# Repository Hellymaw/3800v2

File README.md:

# 3800v2
A personal re-attempt at ENGG3800 project

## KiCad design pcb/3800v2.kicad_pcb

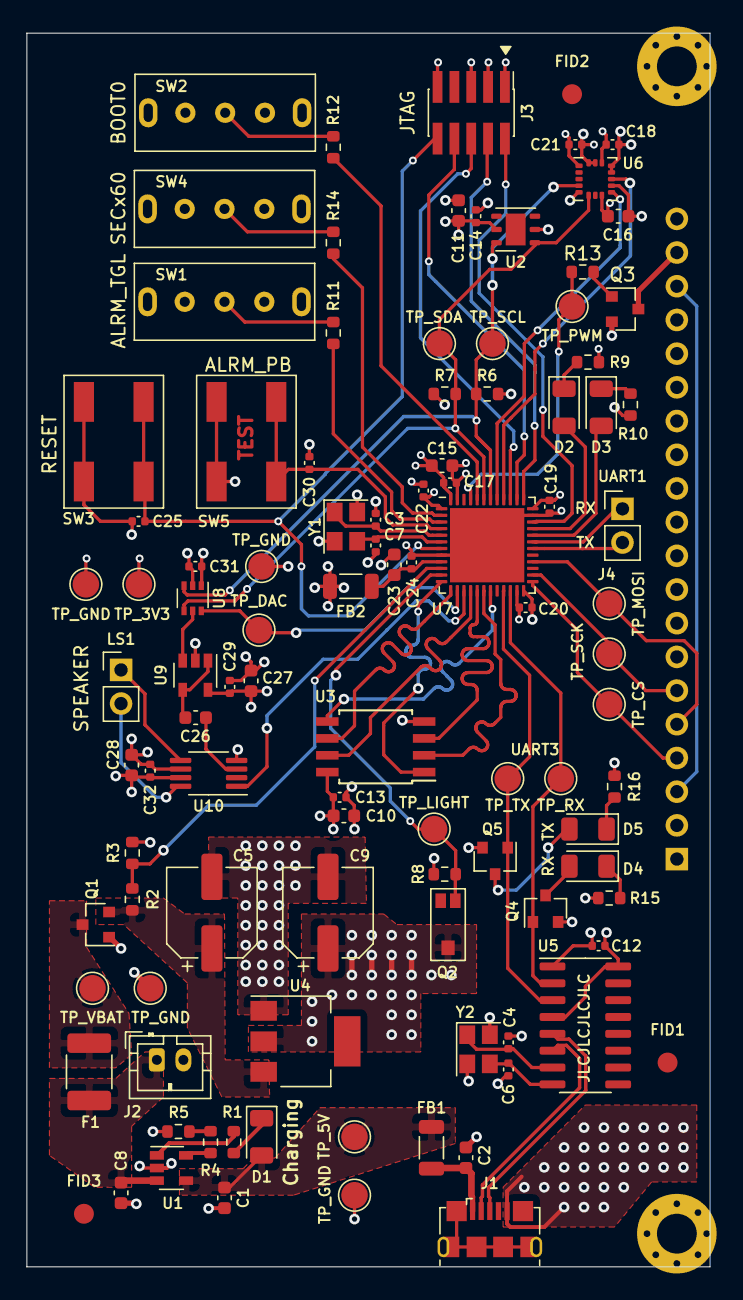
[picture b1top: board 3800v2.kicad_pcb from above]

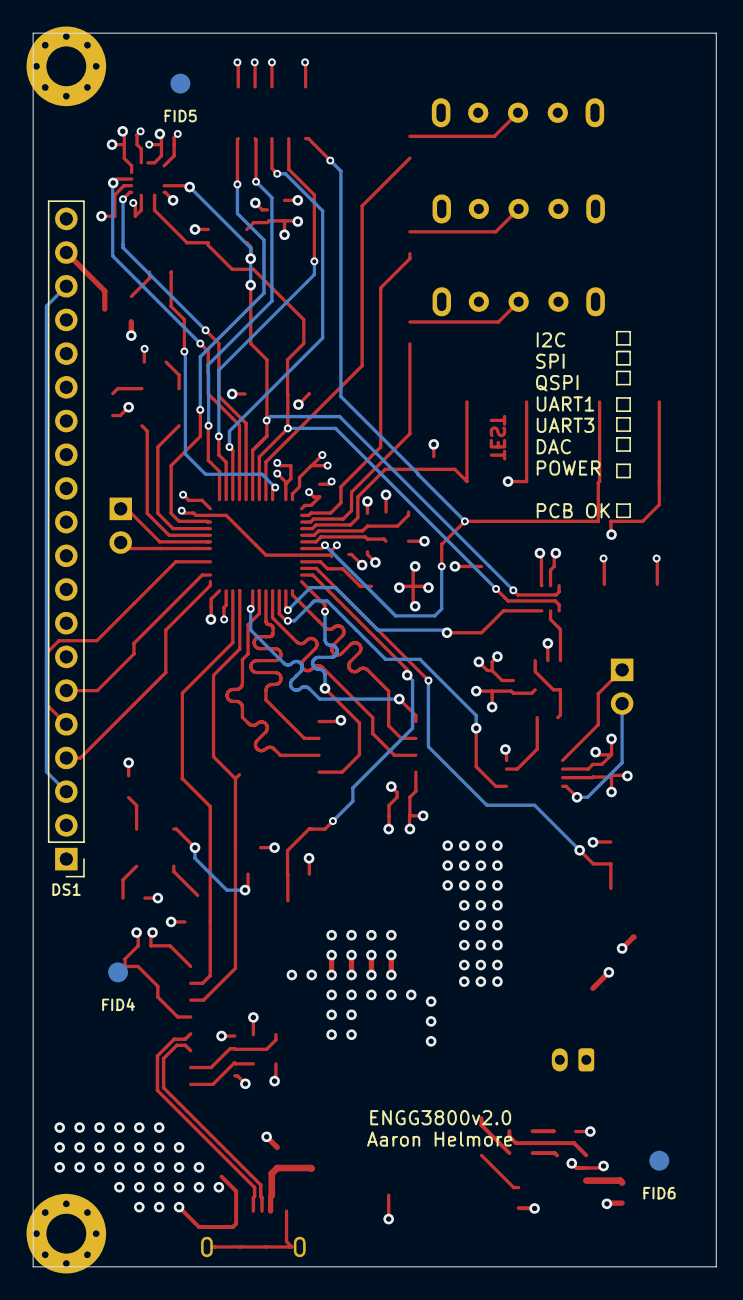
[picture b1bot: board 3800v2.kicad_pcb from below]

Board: 4 copper layers, 51.5 x 93.0 mm, 109 parts (4 on the bottom side), 68 nets.

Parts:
C1, C2, C8, C10, C11, C15, C16, C27, C28: 4.7uF; C_0603_1608Metric
C3, C4, C6, C7: 20pF; C_0402_1005Metric
C5, C9: 47uF; CP_Elec_6.3x7.7
C12, C13, C14, C17, C18, C19, C20, C21, C22, C25, C29, C30, C31, C32: 100nF; C_0402_1005Metric
C23, C26: 1uF; C_0603_1608Metric
C24: 10nF; C_0402_1005Metric
D1, D2, D3, D5: RED; LED_1206_3216Metric
D4: GREEN; LED_1206_3216Metric
DS1: ST7920; PinHeader_1x20_P2.54mm_Vertical
F1: 16V 1.5A; Fuse_1812_4532Metric_Castellated
FB1, FB2: 100 @ 100MHz; L_1206_3216Metric
FID1, FID2, FID3, FID4, FID5, FID6: Fiducial; Fiducial_1.5mm_Mask3mm
H1, H2: M2.5mm; MountingHole_3mm_Pad_Via
J1: USB_B_Micro; USB_Micro-B_Amphenol_10118193_Horizontal
J2: JST PH 1x2; JST_PH_B2B-PH-K_1x02_P2.00mm_Vertical
J3: Conn_ARM_JTAG_SWD_10; PinHeader_2x05_P1.27mm_Vertical_SMD
J4: Conn_01x02; PinHeader_1x02_P2.54mm_Vertical
LS1: 8 Ohm Speaker; PinHeader_1x02_P2.54mm_Vertical
Q1, Q3, Q4, Q5: SL2301S; SOT-23
Q2: TEMT6000X01
R1, R4, R5, R9, R10, R13, R15, R16: 1K; R_0603_1608Metric
R2, R3: 100k; R_0603_1608Metric
R6, R7: 4k7; R_0603_1608Metric
R8, R11, R12, R14: 10K; R_0603_1608Metric
SW1, SW2, SW4: SW_SPDT; Toggle_SW_SPDT_C136718
SW3, SW5: SW_Push_Dual; Tactile_SW_SPST_C412375
TP_3V3: 3V3; TestPoint_Pad_D2.0mm
TP_5V: 5V; TestPoint_Pad_D2.0mm
TP_CS: LCD_CS; TestPoint_Pad_D2.0mm
TP_DAC: DAC; TestPoint_Pad_D2.0mm
TP_GND: GND; TestPoint_Pad_D2.0mm
TP_GND#2, TP_GND#3, TP_GND#4: GND; TestPoint_Pad_D2.0mm
TP_LIGHT: LGHT_SEN; TestPoint_Pad_D2.0mm
TP_MOSI: LCD_SI; TestPoint_Pad_D2.0mm
TP_PWM: LCD_PWM; TestPoint_Pad_D2.0mm
TP_RX: RX1; TestPoint_Pad_D2.0mm
TP_SCK: LCD_SCK; TestPoint_Pad_D2.0mm
TP_SCL: SCL1; TestPoint_Pad_D2.0mm
TP_SDA: SDA1; TestPoint_Pad_D2.0mm
TP_TX: TX1; TestPoint_Pad_D2.0mm
TP_VBAT: VBAT; TestPoint_Pad_D2.0mm
U1: MCP73832; SOT-23-5
U2: Si7006; DFN-6-1EP_3x3mm_P1mm_EP1.5x2.4mm
U3: SST26VF016B; SOIJ-8_5.3x5.3mm_P1.27mm
U4: LM1117-3.3; SOT-223
U5: CH340G; SOIC-16_3.9x9.9mm_P1.27mm
U6: LIS3DH; LGA-16_3x3mm_P0.5mm_LayoutBorder3x5y
U7: STM32L451CCUx; QFN-48-1EP_7x7mm_P0.5mm_EP5.6x5.6mm
U8: MCP4018-503E/LT; SOT-363_SC-70-6
U9: MCP6L01T-E/OT; SOT-23-5
U10: PAM8302AAD; MSOP-8_3x3mm_P0.65mm
Y1: Crystal_GND24; Crystal_SMD_3225-4Pin_3.2x2.5mm
Y2: X322512MSB4SI; Crystal_SMD_3225-4Pin_3.2x2.5mm

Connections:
/D_+: J1.3, U5.5
/D_-: J1.2, U5.6
ADC1_IN5: R2.2, R3.1, U7.10
ADC1_IN6: Q2.1, R8.1, TP_LIGHT.1, U7.11
ALRM_PB: C30.1, SW5.2, SW5.4, U7.4
ALRM_TOGGLE: R11.1, U7.3
BOOT0: R12.1, U7.44
DAC_OUT: TP_DAC.1, U7.14, U8.6
GND: C1.2, C2.2, C3.2, C4.2, C5.2, C6.2, C7.2, C8.2, C9.2, C10.2, C11.2, C12.2, C13.2, C14.2, C15.2, C16.2, C17.2, C18.2, C19.2, C20.2, C21.2, C22.2, C23.2, C24.2, C25.2, C27.2, C28.2, C29.2, C30.2, C31.2, C32.2, DS1.1, DS1.15, DS1.20, J1.5, J2.2, J3.3, J3.5, J3.9, Q1.1, R3.2, R5.2, R8.2, R9.2, R10.2, R15.2, R16.2, SW1.1, SW2.1, SW3.1, SW3.3, SW4.1, SW5.1, SW5.3, TP_GND.1, TP_GND#2.1, TP_GND#3.1, TP_GND#4.1, U1.2, U2.2, U3.4, U4.1, U5.1, U6.5, U6.10, U6.12, U6.13, U6.15, U6.16, U7.8, U7.23, U7.35, U7.47, U7.49, U8.2, U9.2, U10.4, U10.7, Y1.2, Y1.4, Y2.2, Y2.4
I2C1_SCL: R6.2, TP_SCL.1, U2.6, U6.4, U7.42, U8.3
I2C1_SDA: R7.2, TP_SDA.1, U2.1, U6.6, U7.43, U8.4
LCD_CS: DS1.4, TP_CS.1, U7.25
LIS3DH_INT1: U6.11, U7.40
LIS3DH_INT2: U6.9, U7.41
NRST: C25.1, J3.10, SW3.2, SW3.4, U7.7
unnamed: C2.1, FB1.2, J1.1
unnamed: C4.1, U5.7, Y2.1
unnamed: C5.1, Q1.2, R2.1, U4.3
unnamed: C6.1, U5.8, Y2.3
unnamed: C8.1, F1.2, J2.1, U1.3
unnamed: C26.1, U9.1, U9.4
unnamed: C26.2, U10.3
unnamed: D1.1, R1.1
unnamed: D2.1, R9.1
unnamed: D2.2, U7.33
unnamed: D3.1, R10.1
unnamed: D3.2, U7.32
unnamed: D4.1, R15.1
unnamed: D4.2, Q4.3
unnamed: D5.1, R16.1
unnamed: D5.2, Q5.3
unnamed: DS1.3, DS1.18
unnamed: DS1.19, Q3.3
unnamed: LS1.1, U10.5
unnamed: LS1.2, U10.8
unnamed: Q3.1, R13.1
unnamed: R1.2, U1.1
unnamed: R4.1, U1.5
unnamed: R4.2, R5.1
unnamed: R11.2, SW1.2
unnamed: R12.2, SW2.2
unnamed: R14.2, SW4.2
unnamed: U8.5, U9.3
QSPI_CLK: U3.6, U7.13
QSPI_IO0: U3.5, U7.19
QSPI_IO1: U3.2, U7.18
QSPI_IO2: U3.3, U7.17
QSPI_IO3: U3.7, U7.16
QSPI_NCS: U3.1, U7.12
RCC_OSC_IN: C3.1, U7.5, Y1.1
RCC_OSC_OUT: C7.1, U7.6, Y1.3
SECx60: R14.1, U7.2
SPI_MOSI: DS1.5, TP_MOSI.1, U7.28
SPI_SCK: DS1.6, TP_SCK.1, U7.26
SYS_JTCK_SWCLK: J3.4, U7.37
SYS_JTDI: J3.8, U7.38
SYS_JTDO_SWO: J3.6, U7.39
SYS_JTMS_SWDIO: J3.2, U7.34
TIM16_CH1: R13.2, TP_PWM.1, U7.45
USART1_RX: J4.1, U7.31
USART1_TX: J4.2, U7.30
USART3_RX: Q4.1, TP_RX.1, U5.2, U7.22
USART3_TX: Q5.1, TP_TX.1, U5.3, U7.21
VBAT: F1.1, Q1.3, TP_VBAT.1
VDD: C9.1, C10.1, C11.1, C12.1, C13.1, C14.1, C15.1, C16.1, C17.1, C18.1, C19.1, C20.1, C21.1, C22.1, C27.1, C28.1, C29.1, C31.1, C32.1, DS1.2, FB2.2, J3.1, Q2.2, Q3.2, Q4.2, Q5.2, R6.1, R7.1, SW1.3, SW2.3, SW4.3, TP_3V3.1, U2.5, U3.8, U4.2, U5.4, U5.16, U6.1, U6.8, U6.14, U7.1, U7.24, U7.36, U7.48, U8.1, U9.5, U10.6
VDDA: C23.1, C24.1, FB2.1, U7.9
VUSB: C1.1, D1.2, FB1.1, TP_5V.1, U1.4
nAUDIO_SD: U7.15, U10.1

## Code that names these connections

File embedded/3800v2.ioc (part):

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Mcu.Name=STM32L451C(C-E)Ux
Mcu.Package=UFQFPN48
Mcu.UserName=STM32L451CCUx
PA0.GPIOParameters=GPIO_Label
PA0.GPIO_Label=ADC1_BAT
PA0.Signal=ADCx_IN5
PA1.GPIOParameters=GPIO_Label
PA1.GPIO_Label=ADC1_LIGHT
PA1.Signal=ADCx_IN6
PA10.Mode=Asynchronous
PA10.Signal=USART1_RX
PA11.GPIOParameters=GPIO_Label
PA11.GPIO_Label=LED_2
PA11.Signal=GPIO_Output
PA12.GPIOParameters=GPIO_Label
PA12.GPIO_Label=LED_1
PA12.Signal=GPIO_Output
PA13\ (JTMS/SWDIO).Mode=JTAG_4_pins
PA13\ (JTMS/SWDIO).Signal=SYS_JTMS-SWDIO
PA14\ (JTCK/SWCLK).Mode=JTAG_4_pins
PA14\ (JTCK/SWCLK).Signal=SYS_JTCK-SWCLK
PA15\ (JTDI).Mode=JTAG_4_pins
PA15\ (JTDI).Signal=SYS_JTDI
PA2.Mode=Single Bank 1
PA2.Signal=QUADSPI_BK1_NCS
PA3.Mode=Single Bank 1
PA3.Signal=QUADSPI_CLK
PA4.Signal=COMP_DAC11_group
PA5.GPIOParameters=PinState,GPIO_PuPd,GPIO_Label,GPIO_ModeDefaultOutputPP
PA5.GPIO_Label=nPAM_SD
PA5.GPIO_ModeDefaultOutputPP=GPIO_MODE_OUTPUT_OD
PA5.GPIO_PuPd=GPIO_PULLUP
PA5.PinState=GPIO_PIN_SET
PA5.Signal=GPIO_Output
PA6.Mode=Single Bank 1
PA6.Signal=QUADSPI_BK1_IO3
PA7.Mode=Single Bank 1
PA7.Signal=QUADSPI_BK1_IO2
PA8.GPIOParameters=GPIO_Label
PA8.GPIO_Label=LCD_CS
PA8.Signal=GPIO_Output
PA9.Mode=Asynchronous
PA9.Signal=USART1_TX
PB0.Mode=Single Bank 1
PB0.Signal=QUADSPI_BK1_IO1
PB1.Mode=Single Bank 1
PB1.Signal=QUADSPI_BK1_IO0
PB10.Mode=Asynchronous
PB10.Signal=USART3_TX
PB11.Mode=Asynchronous
PB11.Signal=USART3_RX
PB13.Mode=Simplex_Bidirectional_Master
PB13.Signal=SPI2_SCK
PB15.Mode=Simplex_Bidirectional_Master
PB15.Signal=SPI2_MOSI
PB3\ (JTDO/TRACESWO).Mode=JTAG_4_pins
PB3\ (JTDO/TRACESWO).Signal=SYS_JTDO-SWO
PB4\ (NJTRST).GPIOParameters=GPIO_Label
PB4\ (NJTRST).GPIO_Label=LIS3DH_INT1
PB4\ (NJTRST).Signal=GPXTI4
PB5.GPIOParameters=GPIO_Label
PB5.GPIO_Label=LIS3DH_INT2
PB5.Signal=GPXTI5
PB6.Mode=I2C
PB6.Signal=I2C1_SCL
PB7.Mode=I2C
PB7.Signal=I2C1_SDA
PB8.GPIOParameters=GPIO_Label
PB8.GPIO_Label=LCD_PWM
PB8.Signal=S_TIM16_CH1
PC13.GPIOParameters=GPIO_Label,GPIO_ModeDefaultEXTI
PC13.GPIO_Label=SECx60
PC13.GPIO_ModeDefaultEXTI=GPIO_MODE_IT_RISING_FALLING
PC13.Signal=GPXTI13
PC14-OSC32_IN\ (PC14).GPIOParameters=GPIO_Label,GPIO_ModeDefaultEXTI
PC14-OSC32_IN\ (PC14).GPIO_Label=ALRM_TGL
PC14-OSC32_IN\ (PC14).GPIO_ModeDefaultEXTI=GPIO_MODE_IT_RISING_FALLING
PC14-OSC32_IN\ (PC14).Signal=GPXTI14
PC15-OSC32_OUT\ (PC15).GPIOParameters=GPIO_PuPd,GPIO_Label,GPIO_ModeDefaultEXTI
PC15-OSC32_OUT\ (PC15).GPIO_Label=ALRM_PB
PC15-OSC32_OUT\ (PC15).GPIO_ModeDefaultEXTI=GPIO_MODE_IT_FALLING
PC15-OSC32_OUT\ (PC15).GPIO_PuPd=GPIO_PULLUP
PC15-OSC32_OUT\ (PC15).Signal=GPXTI15
PH0-OSC_IN\ (PH0).Mode=HSE-External-Oscillator
PH0-OSC_IN\ (PH0).Signal=RCC_OSC_IN
PH1-OSC_OUT\ (PH1).Mode=HSE-External-Oscillator
PH1-OSC_OUT\ (PH1).Signal=RCC_OSC_OUT
PH3-BOOT0\ (BOOT0).GPIOParameters=GPIO_Label
PH3-BOOT0\ (BOOT0).GPIO_Label=BOOT0
PH3-BOOT0\ (BOOT0).Signal=GPIO_Input
RCC.HSE_VALUE=16000000
RCC.SYSCLKFreq_VALUE=80000000
RCC.SYSCLKSource=RCC_SYSCLKSOURCE_PLLCLK
board=custom

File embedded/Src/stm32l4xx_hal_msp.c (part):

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  
    __HAL_RCC_GPIOA_CLK_ENABLE();
    /**ADC1 GPIO Configuration    
    PA0     ------> ADC1_IN5
    PA1     ------> ADC1_IN6 
    */
    GPIO_InitStruct.Pin = ADC1_BAT_Pin|ADC1_LIGHT_Pin;
    GPIO_InitStruct.Mode = GPIO_MODE_ANALOG_ADC_CONTROL;
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    __HAL_RCC_ADC_CLK_DISABLE();
  
    /**ADC1 GPIO Configuration    
    PA0     ------> ADC1_IN5
    PA1     ------> ADC1_IN6 
    */
    HAL_GPIO_DeInit(GPIOA, ADC1_BAT_Pin|ADC1_LIGHT_Pin);

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  
    __HAL_RCC_GPIOB_CLK_ENABLE();
    /**I2C1 GPIO Configuration    
    PB6     ------> I2C1_SCL
    PB7     ------> I2C1_SDA 
    */
    GPIO_InitStruct.Pin = GPIO_PIN_6|GPIO_PIN_7;
    GPIO_InitStruct.Mode = GPIO_MODE_AF_OD;
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    __HAL_RCC_I2C1_CLK_DISABLE();
  
    /**I2C1 GPIO Configuration    
    PB6     ------> I2C1_SCL
    PB7     ------> I2C1_SDA 
    */
    HAL_GPIO_DeInit(GPIOB, GPIO_PIN_6|GPIO_PIN_7);

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  
    __HAL_RCC_GPIOB_CLK_ENABLE();
    /**TIM16 GPIO Configuration    
    PB8     ------> TIM16_CH1 
    */
    GPIO_InitStruct.Pin = LCD_PWM_Pin;
    GPIO_InitStruct.Mode = GPIO_MODE_AF_PP;
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  
    __HAL_RCC_GPIOA_CLK_ENABLE();
    /**USART1 GPIO Configuration    
    PA9     ------> USART1_TX
    PA10     ------> USART1_RX 
    */
    GPIO_InitStruct.Pin = GPIO_PIN_9|GPIO_PIN_10;
    GPIO_InitStruct.Mode = GPIO_MODE_AF_PP;
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  
    __HAL_RCC_GPIOB_CLK_ENABLE();
    /**USART3 GPIO Configuration    
    PB10     ------> USART3_TX
    PB11     ------> USART3_RX 
    */
    GPIO_InitStruct.Pin = GPIO_PIN_10|GPIO_PIN_11;
    GPIO_InitStruct.Mode = GPIO_MODE_AF_PP;
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    __HAL_RCC_USART1_CLK_DISABLE();
  
    /**USART1 GPIO Configuration    
    PA9     ------> USART1_TX
    PA10     ------> USART1_RX 
    */
    HAL_GPIO_DeInit(GPIOA, GPIO_PIN_9|GPIO_PIN_10);

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    __HAL_RCC_USART3_CLK_DISABLE();
  
    /**USART3 GPIO Configuration    
    PB10     ------> USART3_TX
    PB11     ------> USART3_RX 
    */
    HAL_GPIO_DeInit(GPIOB, GPIO_PIN_10|GPIO_PIN_11);

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
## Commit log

2021-01-19 Initial commit of source files
    Initial files for firmware source and pcb source

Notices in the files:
embedded/Src/stm32l4xx_hal_msp.c:
© Copyright (c) 2021 STMicroelectronics.
All rights reserved.
This software component is licensed by ST under BSD 3-Clause license,
the "License"; You may not use this file except in compliance with the
License. You may obtain a copy of the License at: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
(C) COPYRIGHT STMicroelectronics *****END OF FILE
